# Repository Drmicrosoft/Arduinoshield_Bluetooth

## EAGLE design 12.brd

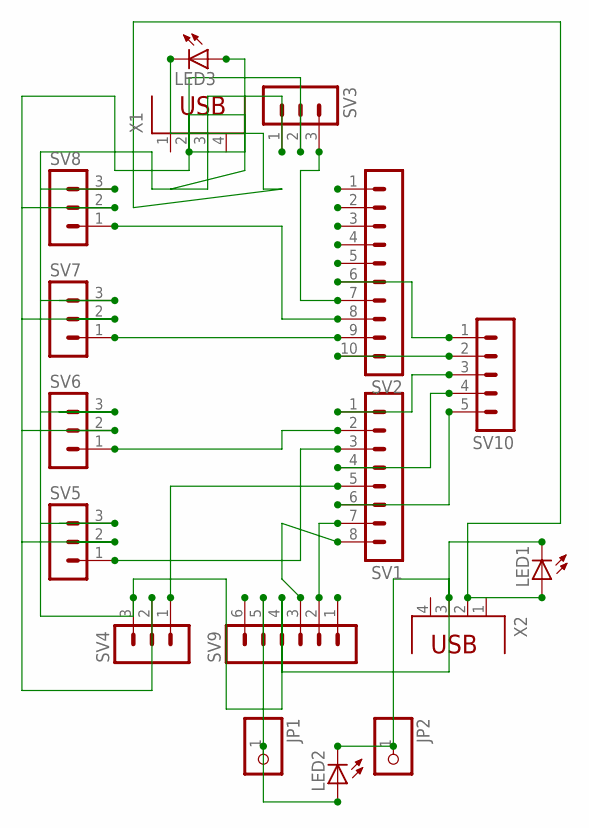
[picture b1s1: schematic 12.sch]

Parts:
JP1, JP2: PINHD-1X1; 1X01
LED1, LED2, LED3: LEDLD260; LD260
SV1: MA08-1
SV2: MA10-1
SV3, SV4, SV5, SV6, SV7, SV8: MA03-1
SV9: MA06-1
SV10: MA05-1
X1, X2: PN61729

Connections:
unnamed: SV2.7, SV3.3
unnamed: JP1.1, LED2.A, SV9.5
unnamed: LED1.A, LED3.A, SV3.2, SV4.2, SV5.2, SV6.2, SV7.2, SV8.2, X1.2, X2.2
unnamed: SV2.8, SV8.1
unnamed: SV2.9, SV7.1
unnamed: SV1.2, SV6.1
unnamed: SV1.3, SV5.1
unnamed: SV1.5, SV4.1
unnamed: SV1.8, SV9.3
unnamed: SV1.7, SV9.2
unnamed: SV1.6, SV10.5
unnamed: SV1.4, SV10.4
unnamed: SV1.1, SV10.3
unnamed: SV2.10, SV10.2
unnamed: SV2.6, SV10.1
OMAR: JP2.1, LED1.K (C), LED2.K (C), LED3.K (C), SV3.1, SV4.3, SV5.3, SV6.3, SV7.3, SV8.3, SV9.4, X1.3, X2.3

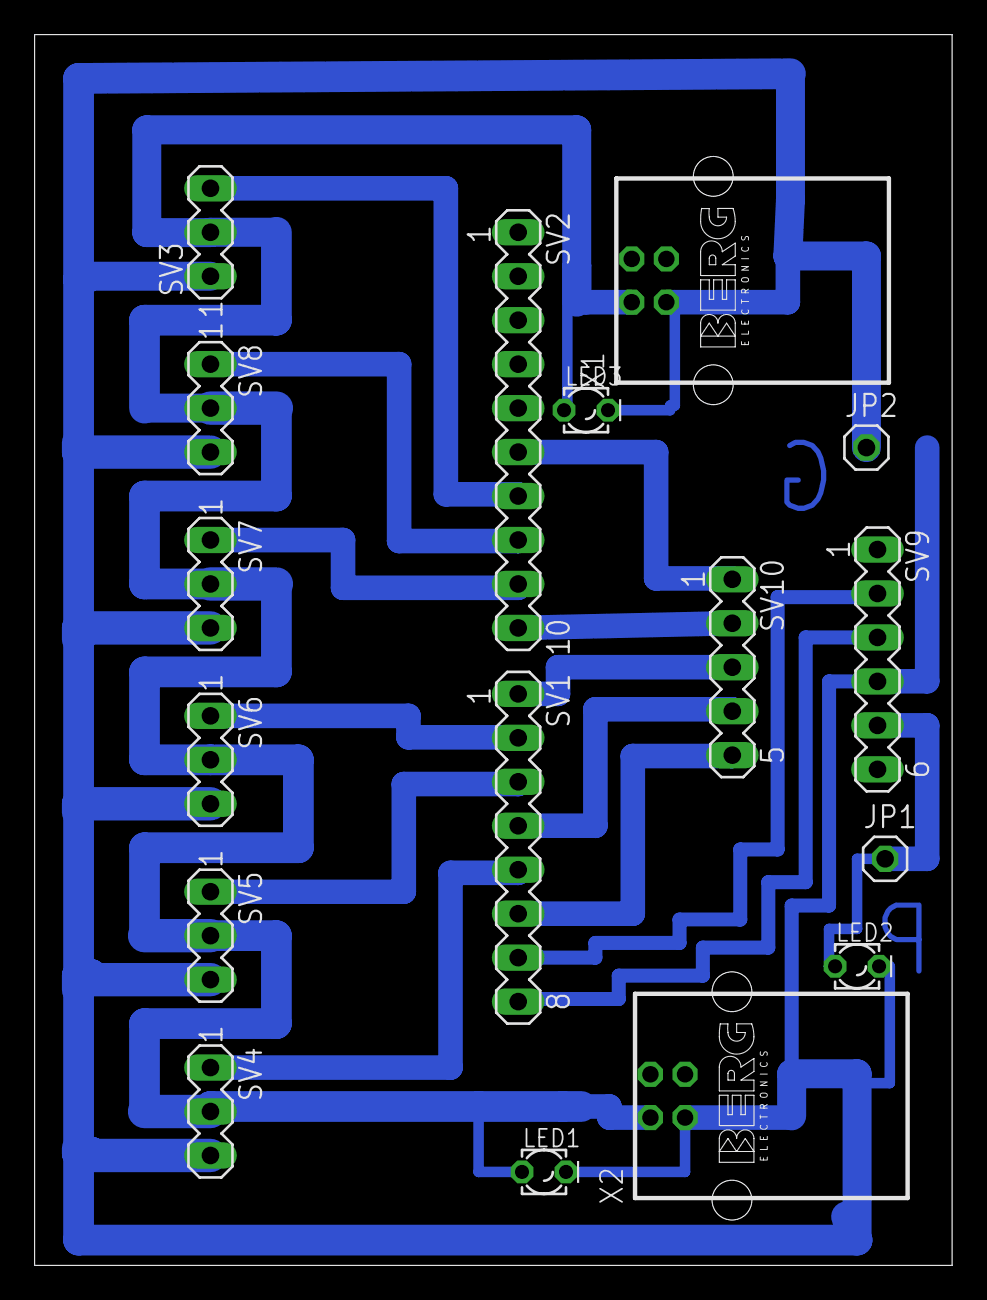
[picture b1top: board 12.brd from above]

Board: 2 copper layers, 53.0 x 71.1 mm, 17 parts (0 on the bottom side), 16 nets.
